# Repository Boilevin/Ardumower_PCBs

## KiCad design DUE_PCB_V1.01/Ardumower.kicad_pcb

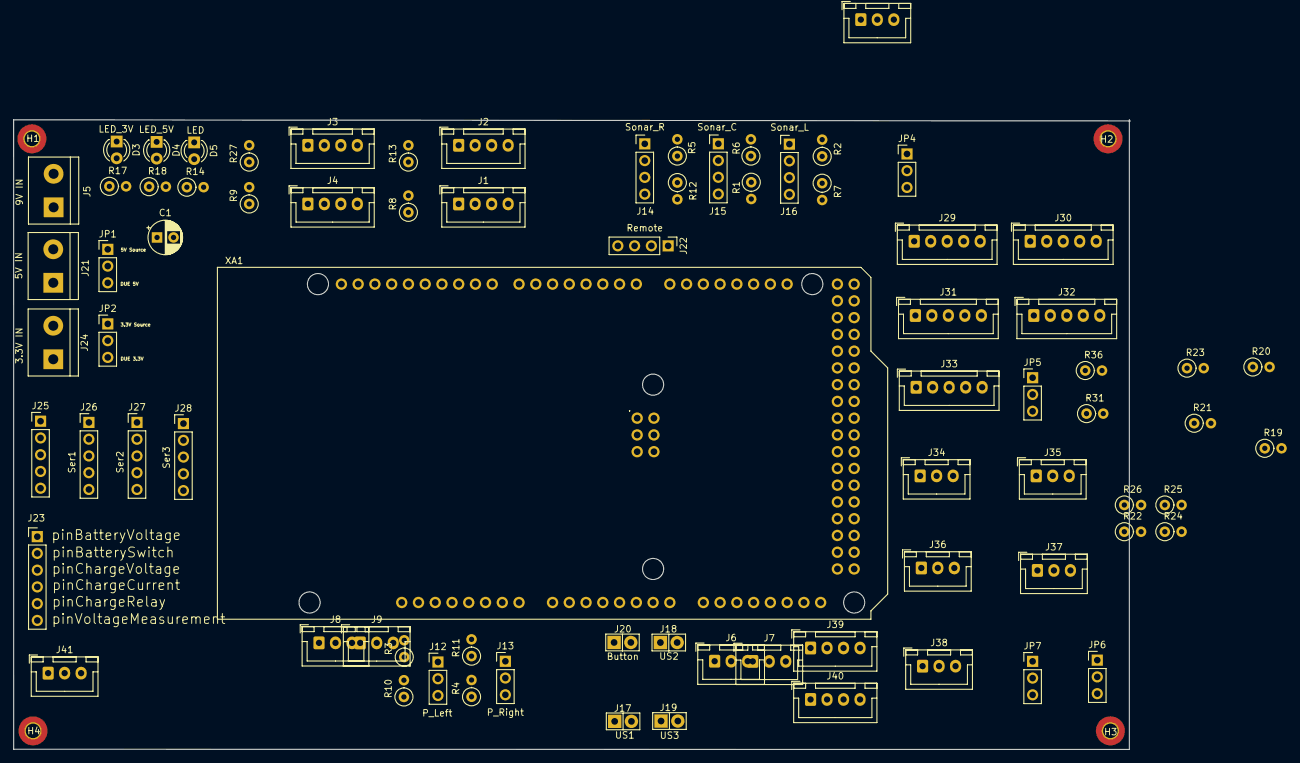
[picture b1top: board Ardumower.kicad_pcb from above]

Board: 2 copper layers, 169.3 x 95.5 mm, 82 parts (0 on the bottom side), 92 nets, no tracks yet.

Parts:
C1: 100nF; CP_Radial_D5.0mm_P2.50mm
D3: LED_3V; LED_D3.0mm
D4: LED_5V; LED_D3.0mm
D5: LED; LED_D3.0mm
H1, H2, H3, H4: MountingHole_Pad; MountingHole_2.2mm_M2_Pad_TopBottom
J1: I2C0_1; JST_XH_B4B-XH-A_1x04_P2.50mm_Vertical
J2: I2C0_2; JST_XH_B4B-XH-A_1x04_P2.50mm_Vertical
J3: I2C1_1; JST_XH_B4B-XH-A_1x04_P2.50mm_Vertical
J4: I2C1_2; JST_XH_B4B-XH-A_1x04_P2.50mm_Vertical
J5: 9V IN; TerminalBlock_bornier-2_P5.08mm
J6: Drop_Left; JST_XH_B3B-XH-A_1x03_P2.50mm_Vertical
J7: Drop_Right; JST_XH_B3B-XH-A_1x03_P2.50mm_Vertical
J8: Tilt; JST_XH_B3B-XH-A_1x03_P2.50mm_Vertical
J9: Rain; JST_XH_B3B-XH-A_1x03_P2.50mm_Vertical
J10: Bumper; JST_XH_B3B-XH-A_1x03_P2.50mm_Vertical
J12: P_Left; PinHeader_1x03_P2.54mm_Vertical
J13: P_Right; PinHeader_1x03_P2.54mm_Vertical
J14: Sonar_R; PinHeader_1x04_P2.54mm_Vertical
J15: Sonar_C; PinHeader_1x04_P2.54mm_Vertical
J16: Sonar_L; PinHeader_1x04_P2.54mm_Vertical
J17: US1; Pin_Header_KK110_1x02_3D
J18: US2; Pin_Header_KK110_1x02_3D
J19: US3; Pin_Header_KK110_1x02_3D
J20: Button; Pin_Header_KK110_1x02_3D
J21: 5V IN; TerminalBlock_bornier-2_P5.08mm
J22: Remote; PinHeader_1x04_P2.54mm_Vertical
J23: PCB_2; PinHeader_1x06_P2.54mm_Vertical
J24: 3.3V IN; TerminalBlock_bornier-2_P5.08mm
J25: Ser0; PinHeader_1x05_P2.54mm_Vertical
J26: Ser1; PinHeader_1x05_P2.54mm_Vertical
J27: Ser2; PinHeader_1x05_P2.54mm_Vertical
J28: Ser3; PinHeader_1x05_P2.54mm_Vertical
J29: Motor_Right1; JST_XH_B5B-XH-A_1x05_P2.50mm_Vertical
J30: Motor_Right2; JST_XH_B5B-XH-A_1x05_P2.50mm_Vertical
J31: Motor_Left1; JST_XH_B5B-XH-A_1x05_P2.50mm_Vertical
J32: Motor_Left2; JST_XH_B5B-XH-A_1x05_P2.50mm_Vertical
J33: Cutter_Motor; JST_XH_B5B-XH-A_1x05_P2.50mm_Vertical
J34: ODORight1; JST_XH_B3B-XH-A_1x03_P2.50mm_Vertical
J35: ODORight2; JST_XH_B3B-XH-A_1x03_P2.50mm_Vertical
J36: ODOLeft1; JST_XH_B3B-XH-A_1x03_P2.50mm_Vertical
J37: ODOLeft2; JST_XH_B3B-XH-A_1x03_P2.50mm_Vertical
J38: ODOCutter; JST_XH_B3B-XH-A_1x03_P2.50mm_Vertical
J39: MC33926 compatibility sense; JST_XH_B4B-XH-A_1x04_P2.50mm_Vertical
J40: MC33926 compatibility fault; JST_XH_B4B-XH-A_1x04_P2.50mm_Vertical
J41: Buzzer; JST_XH_B3B-XH-A_1x03_P2.50mm_Vertical
JP1: Jumper_5V; PinHeader_1x03_P2.54mm_Vertical
JP2: Jumper_3.3V; PinHeader_1x03_P2.54mm_Vertical
JP4: Motor_Driver_Power; PinHeader_1x03_P2.54mm_Vertical
JP5: Cutter_Power; PinHeader_1x03_P2.54mm_Vertical
JP6: ODO_Power; PinHeader_1x03_P2.54mm_Vertical
JP7: CRPM_Power; PinHeader_1x03_P2.54mm_Vertical
R1, R2, R3, R4, R5, R19, R20, R21, R22, R31: 1KO; R_Axial_DIN0207_L6.3mm_D2.5mm_P2.54mm_Vertical
R6, R7, R12: 2KO; R_Axial_DIN0207_L6.3mm_D2.5mm_P2.54mm_Vertical
R8, R9, R13, R27: XXX; R_Axial_DIN0207_L6.3mm_D2.5mm_P2.54mm_Vertical
R10, R11, R23, R24, R25, R26, R36: 1.5KO; R_Axial_DIN0207_L6.3mm_D2.5mm_P2.54mm_Vertical
R14, R17: 100; R_Axial_DIN0207_L6.3mm_D2.5mm_P2.54mm_Vertical
R18: 220; R_Axial_DIN0207_L6.3mm_D2.5mm_P2.54mm_Vertical
XA1: Arduino_Due_Shield

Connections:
+3V3: J1.1, J2.1, J3.1, J4.1, J6.1, J7.1, J8.1, J9.1, J25.1, J26.1, J27.1, J28.1, JP2.2, JP4.1, JP5.1, JP6.1, JP7.1, R8.2, R9.2, R13.2, R17.2, R27.2
+5V: J12.1, J13.1, J14.1, J15.1, J16.1, J25.5, J26.5, J27.5, J28.5, J41.1, JP1.2, JP4.3, JP5.3, JP6.3, JP7.3, R18.2
+9V: J5.2, XA1.VIN
DUE_3.3V: JP2.3, XA1.3V3
DUE_5V: JP1.3, XA1.5V1
GND: C1.1, D3.1, D4.1, D5.1, H1.1, H2.1, H3.1, H4.1, J1.2, J2.2, J3.2, J4.2, J5.1, J6.2, J7.2, J8.2, J9.2, J10.1, J12.2, J13.2, J14.2, J15.2, J16.2, J17.1, J18.1, J19.1, J20.1, J21.1, J24.1, J25.2, J26.2, J27.2, J28.2, J29.5, J30.5, J31.5, J32.5, J33.5, J34.3, J35.3, J36.3, J37.3, J38.3, J41.2, R6.2, R7.2, R10.2, R11.2, R12.2, R23.2, R24.2, R25.2, R26.2, R36.2, XA1.GND1, XA1.GND2, XA1.GND3, XA1.GND5, XA1.GND6
unnamed: C1.2, XA1.AREF
unnamed: D3.2, R17.1
unnamed: D4.2, R18.1
unnamed: D5.2, R14.2
unnamed: J12.3, R3.1, R10.1
unnamed: J13.3, R4.1, R11.1
unnamed: J14.3, R5.1, R12.1
unnamed: J15.3, R1.1, R6.1
unnamed: J16.3, R2.1, R7.1
unnamed: J21.2, JP1.1
unnamed: J24.2, JP2.1
unnamed: J29.4, J30.4, J31.4, J32.4, JP4.2
unnamed: J33.4, JP5.2
unnamed: J34.1, R31.2, R36.1
unnamed: J34.2, J35.2, J36.2, J37.2, JP6.2
unnamed: J35.1, R19.2, R23.1
unnamed: J36.1, R20.2, R24.1
unnamed: J37.1, R21.2, R25.1
unnamed: J38.1, R22.2, R26.1
unnamed: J38.2, JP7.2
RX0: J25.3, XA1.D0
RX1: J26.3, XA1.D19
RX2: J27.3, XA1.D17
RX3: J28.3, XA1.D15
SCL0: J1.4, J2.4, R8.1, XA1.D21
SCL1: J3.4, J4.4, R9.1, XA1.SCL1
SDA0: J1.3, J2.3, R13.1, XA1.D20
SDA1: J3.3, J4.3, R27.1, XA1.SDA1
TX0: J25.4, XA1.D1
TX1: J26.4, XA1.D18
TX2: J27.4, XA1.D16
TX3: J28.4, XA1.D14
pinBatterySwitch: J23.2, XA1.D4
pinBatteryVoltage: J23.1, XA1.A2
pinBumperLeft: J10.3, XA1.D39
pinBumperRight: J10.2, XA1.D38
pinButton: J20.2, XA1.D51
pinBuzzer: J41.3, XA1.D53
pinChargeCurrent: J23.4, XA1.A8
pinChargeRelay: J23.5, XA1.D50
pinChargeVoltage: J23.3, XA1.A9
pinDropLeft: J6.3, XA1.D45
pinDropRight: J7.3, XA1.D23
pinLED: R14.1, XA1.D13
pinMotorEnable: J29.3, J30.3, J31.3, J32.3, XA1.D37
pinMotorLeft2Dir: J32.2, XA1.D40
pinMotorLeft2PWM: J32.1, XA1.D6
pinMotorLeftDir: J31.2, XA1.D31
pinMotorLeftFault: J40.2, XA1.D25
pinMotorLeftPWM: J31.1, XA1.D5
pinMotorLeftSense: J39.2, XA1.A1
pinMotorMow1Sense: J39.3, XA1.A6
pinMotorMow2Sense: J39.4, XA1.A3
pinMotorMowDir: J33.2, XA1.D29
pinMotorMowEnable: J33.3, XA1.D28
pinMotorMowFault: J40.3, XA1.D26
pinMotorMowPWM: J33.1, XA1.D2
pinMotorMowRpm: R22.1, XA1.A11
pinMotorRight2Dir: J30.2, XA1.D41
pinMotorRight2PWM: J30.1, XA1.D7
pinMotorRightDir: J29.2, XA1.D33
pinMotorRightFault: J40.1, XA1.D27
pinMotorRightPWM: J29.1, XA1.D3
pinMotorRightSense: J39.1, XA1.A0
pinOdometryLeft: R20.1, XA1.DAC0
pinOdometryLeft2: R21.1, XA1.DAC1
pinOdometryRight: R31.1, XA1.CANR
pinOdometryRight2: R19.1, XA1.CANT
pinPerimeterLeft: R3.2, XA1.A5
pinPerimeterRight: R4.2, XA1.A4
pinRain: J9.3, XA1.D44
pinRemoteMow: J22.3, XA1.D12
pinRemoteSpeed: J22.1, XA1.D10
pinRemoteSteer: J22.2, XA1.D11
pinRemoteSwitch: J22.4, XA1.D52
pinSonarCenterEcho: R1.2, XA1.D22
pinSonarCenterTrigger: J15.4, XA1.D24
pinSonarLeftEcho: R2.2, XA1.D36
pinSonarLeftTrigger: J16.4, XA1.D34
pinSonarRightEcho: R5.2, XA1.D32
pinSonarRightTrigger: J14.4, XA1.D30
pinTilt: J8.3, XA1.D35
pinUserSwitch1: J17.2, XA1.D46
pinUserSwitch2: J18.2, XA1.D47
pinUserSwitch3: J19.2, XA1.D48
pinVoltageMeasurement: J23.6, XA1.A7

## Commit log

2021-05-10 first test
2021-05-10 half job
